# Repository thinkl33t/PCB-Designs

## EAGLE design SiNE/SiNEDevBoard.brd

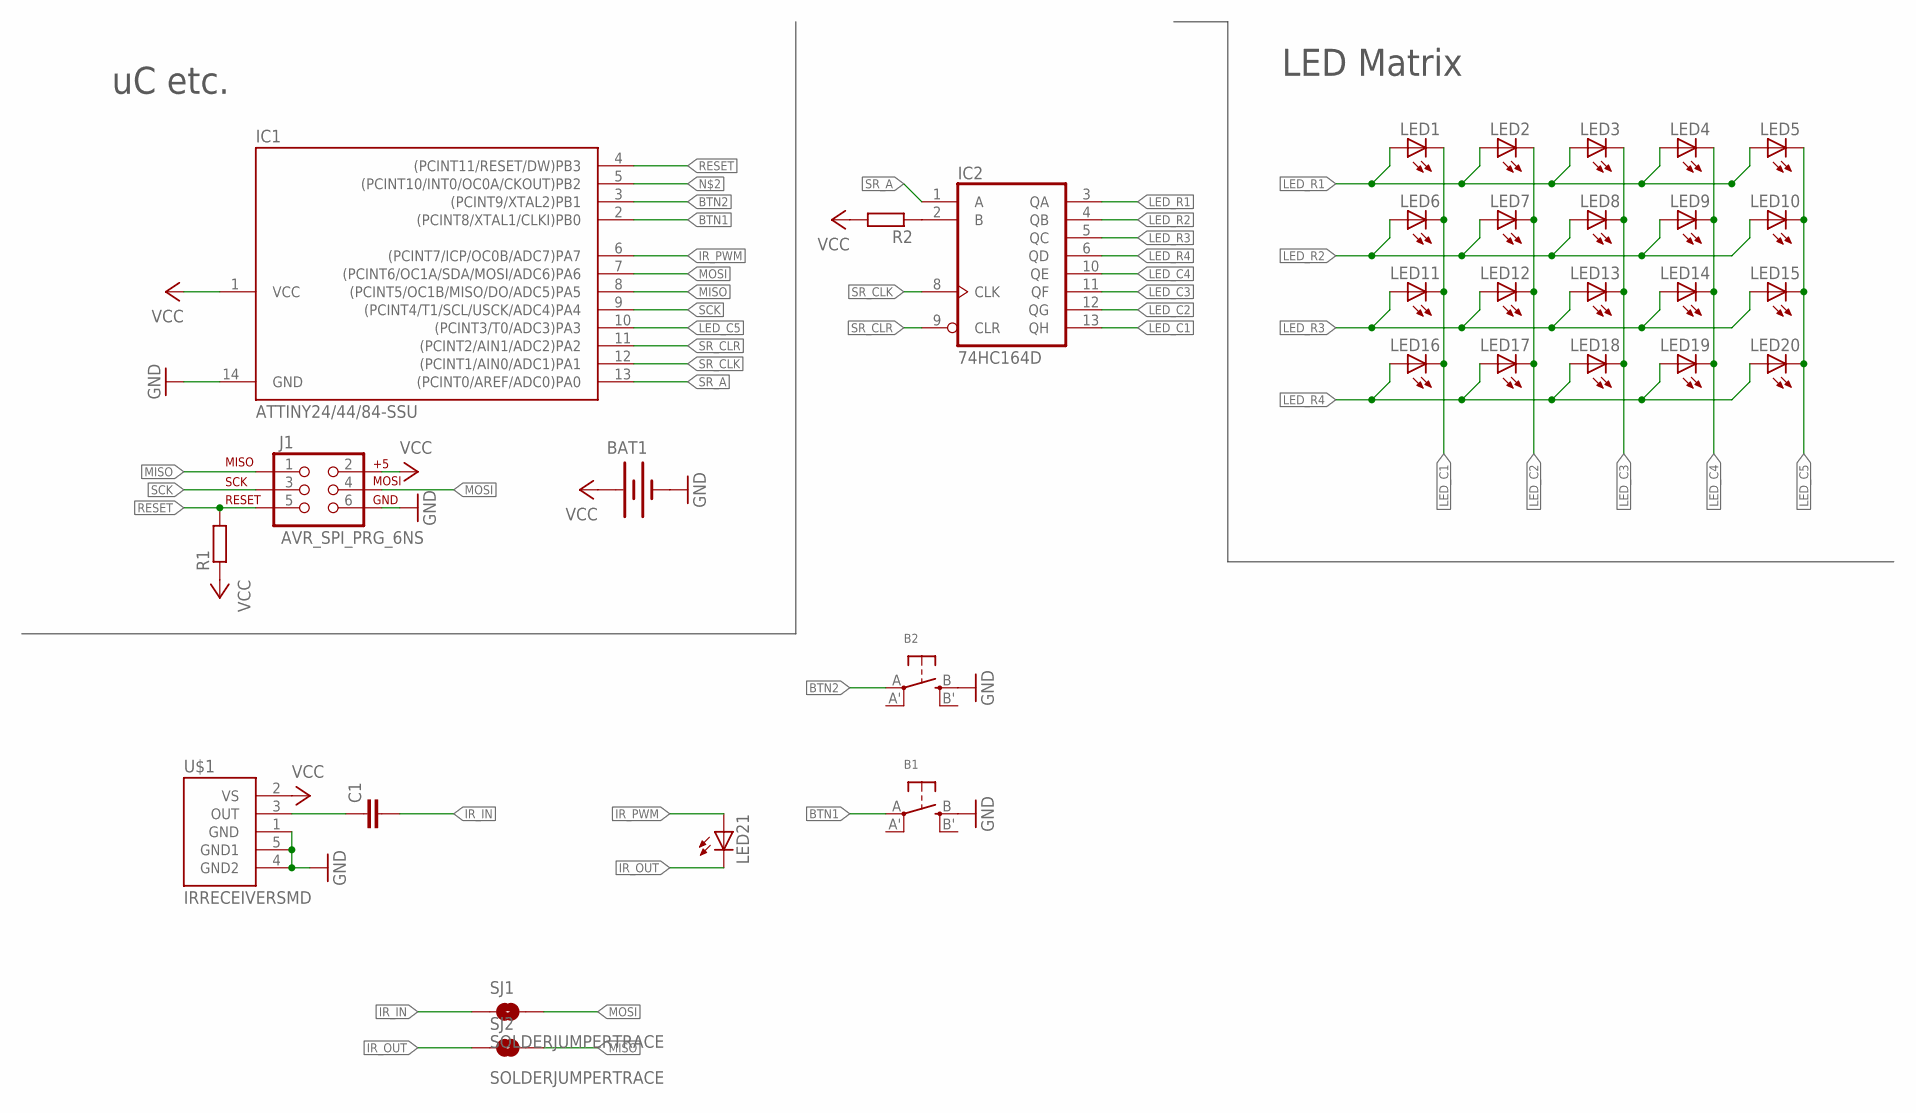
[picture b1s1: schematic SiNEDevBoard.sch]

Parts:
B1, B2: SWITCH_TACT_SMT; EVQ-Q2
BAT1: BATTERY20SMD; BATTCON_20MM
C1: C-EUC0805; C0805
IC1: ATTINY24/44/84-SSU; SOIC14
IC2: 74HC164D; SO14
J1: AVR_SPI_PRG_6NS; 2X3-NS
LED1, LED2, LED3, LED4, LED5, LED6, LED7, LED8, LED9, LED10, LED11, LED12, LED13, LED14, LED15, LED16, LED17, LED18, LED19, LED20: LEDCHIPLED_0805; CHIPLED_0805
LED21: LEDCHIPLED_1206; CHIPLED_1206
R1, R2: R-EU_R0805; R0805
SJ1, SJ2: SOLDERJUMPERTRACE; SJ_2S-TRACE
U$1: IRRECEIVERSMD; TSOP8523

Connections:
BTN1: B1.A, IC1.2 ((PCINT8/XTAL1/CLKI)PB0)
BTN2: B2.A, IC1.3 ((PCINT9/XTAL2)PB1)
GND: B1.B (S), B2.B (S), BAT1.2 (-), IC1.14 (GND), IC2.7 (GND), J1.6, U$1.1 (GND), U$1.4 (GND2), U$1.5 (GND1)
IR_IN: C1.2, SJ1.1
IR_OUT: LED21.C, SJ2.1
IR_PWM: IC1.6 ((PCINT7/ICP/OC0B/ADC7)PA7), LED21.A
LED_C1: IC2.13 (QH), LED1.C, LED6.C, LED11.C, LED16.C
LED_C2: IC2.12 (QG), LED2.C, LED7.C, LED12.C, LED17.C
LED_C3: IC2.11 (QF), LED3.C, LED8.C, LED13.C, LED18.C
LED_C4: IC2.10 (QE), LED4.C, LED9.C, LED14.C, LED19.C
LED_C5: IC1.10 ((PCINT3/T0/ADC3)PA3), LED5.C, LED10.C, LED15.C, LED20.C
LED_R1: IC2.3 (QA), LED1.A, LED2.A, LED3.A, LED4.A, LED5.A
LED_R2: IC2.4 (QB), LED6.A, LED7.A, LED8.A, LED9.A, LED10.A
LED_R3: IC2.5 (QC), LED11.A, LED12.A, LED13.A, LED14.A, LED15.A
LED_R4: IC2.6 (QD), LED16.A, LED17.A, LED18.A, LED19.A, LED20.A
MISO: IC1.8 ((PCINT5/OC1B/MISO/DO/ADC5)PA5), J1.1, SJ2.2
MOSI: IC1.7 ((PCINT6/OC1A/SDA/MOSI/ADC6)PA6), J1.4, SJ1.2
unnamed: IC2.2 (B), R2.1
unnamed: C1.1, U$1.3 (OUT)
RESET: IC1.4 ((PCINT11/RESET/DW)PB3), J1.5, R1.2
SCK: IC1.9 ((PCINT4/T1/SCL/USCK/ADC4)PA4), J1.3
SR_A: IC1.13 ((PCINT0/AREF/ADC0)PA0), IC2.1 (A)
SR_CLK: IC1.12 ((PCINT1/AIN0/ADC1)PA1), IC2.8 (CLK)
SR_CLR: IC1.11 ((PCINT2/AIN1/ADC2)PA2), IC2.9 (CLR)
VCC: BAT1.1 (+), IC1.1 (VCC), IC2.14 (VCC), J1.2, R1.1, R2.2, U$1.2 (VS)

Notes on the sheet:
LED Matrix
uC etc.

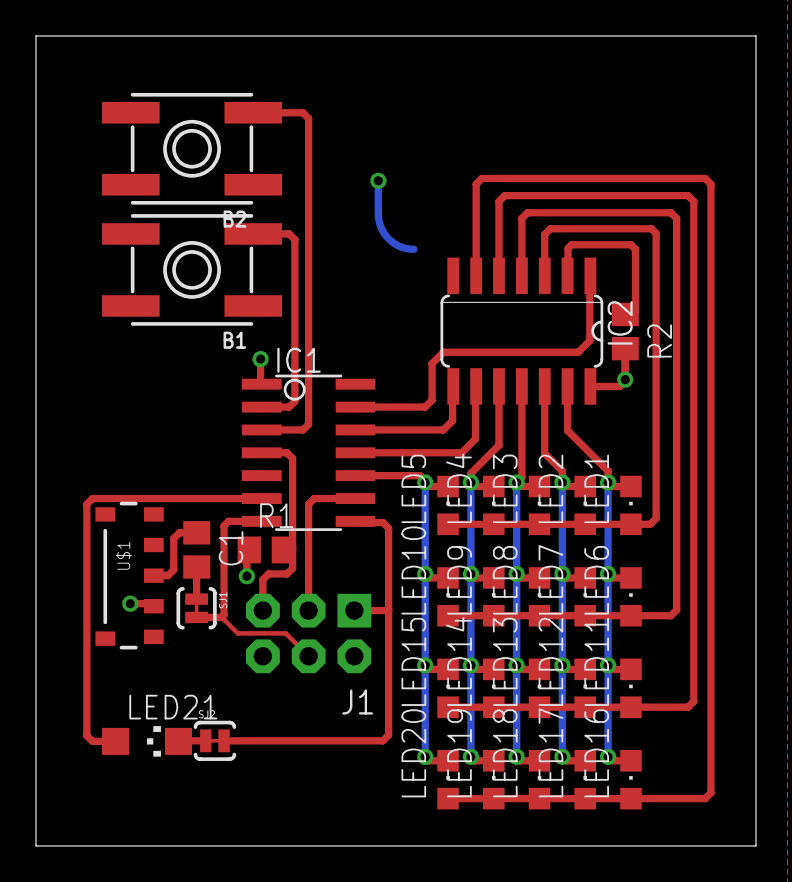
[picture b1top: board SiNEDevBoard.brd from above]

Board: 2 copper layers, 40.0 x 45.0 mm, 33 parts (1 on the bottom side), 25 nets.

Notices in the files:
parts and their libraries:
SparkFun: Licensing: CC v3.0 Share-Alike You are welcome to use this library for commercial purposes.
microbuilder: This work is placed in the public domain, and may be freely used for commercial and non-commercial work with the following conditions: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
